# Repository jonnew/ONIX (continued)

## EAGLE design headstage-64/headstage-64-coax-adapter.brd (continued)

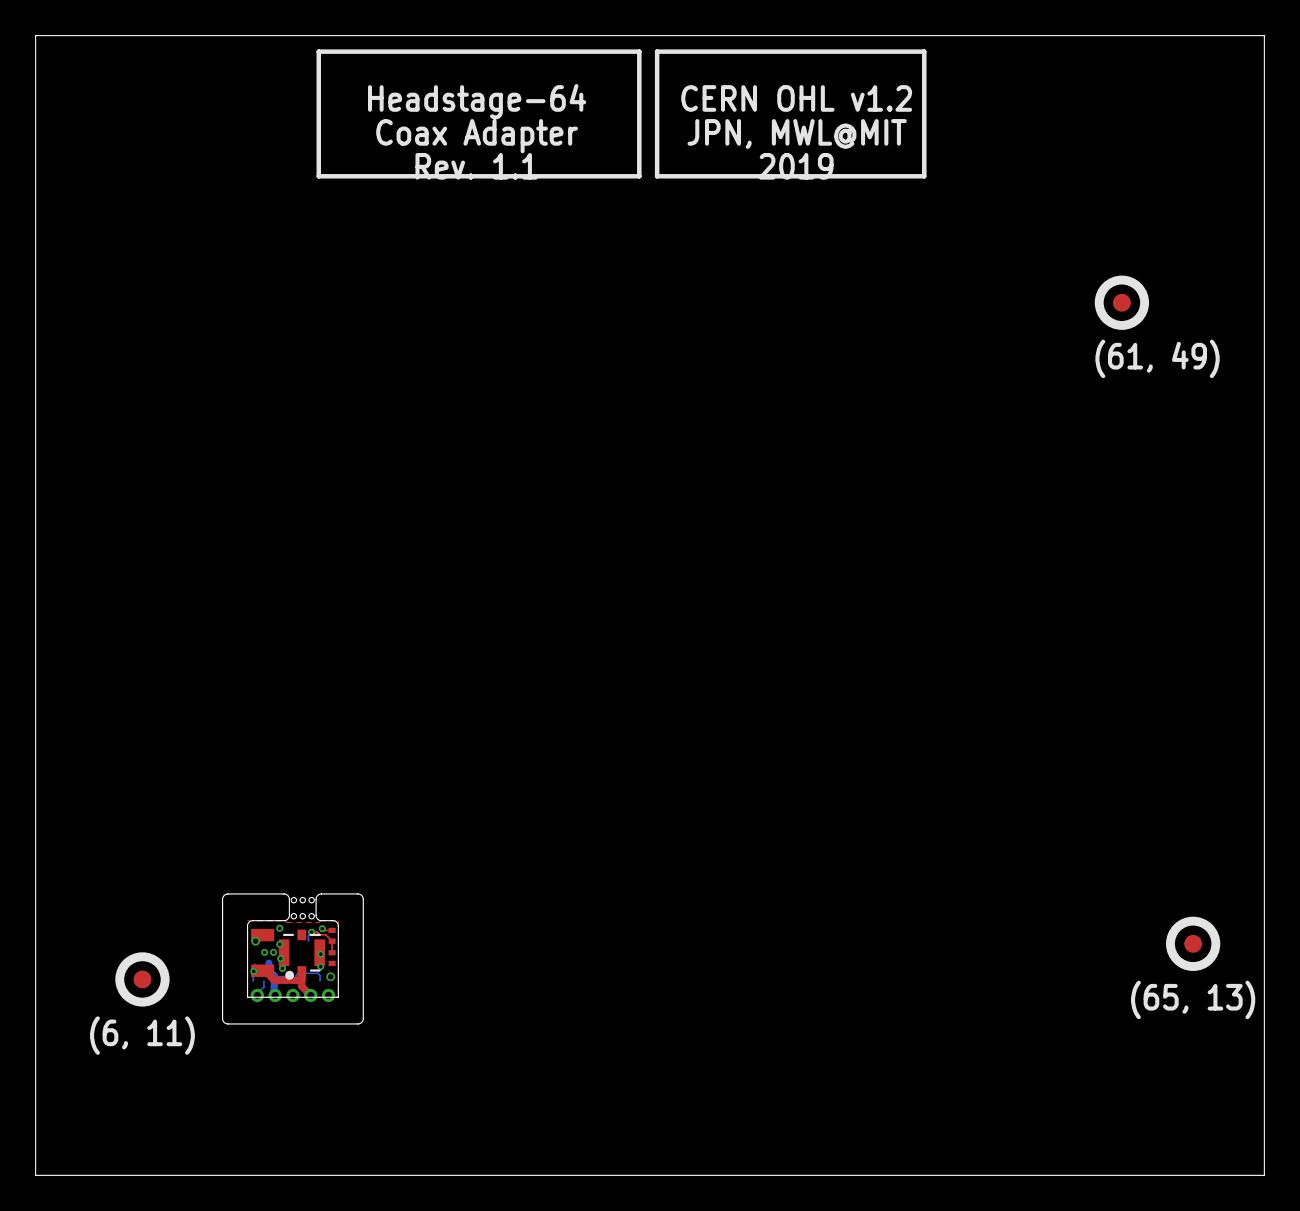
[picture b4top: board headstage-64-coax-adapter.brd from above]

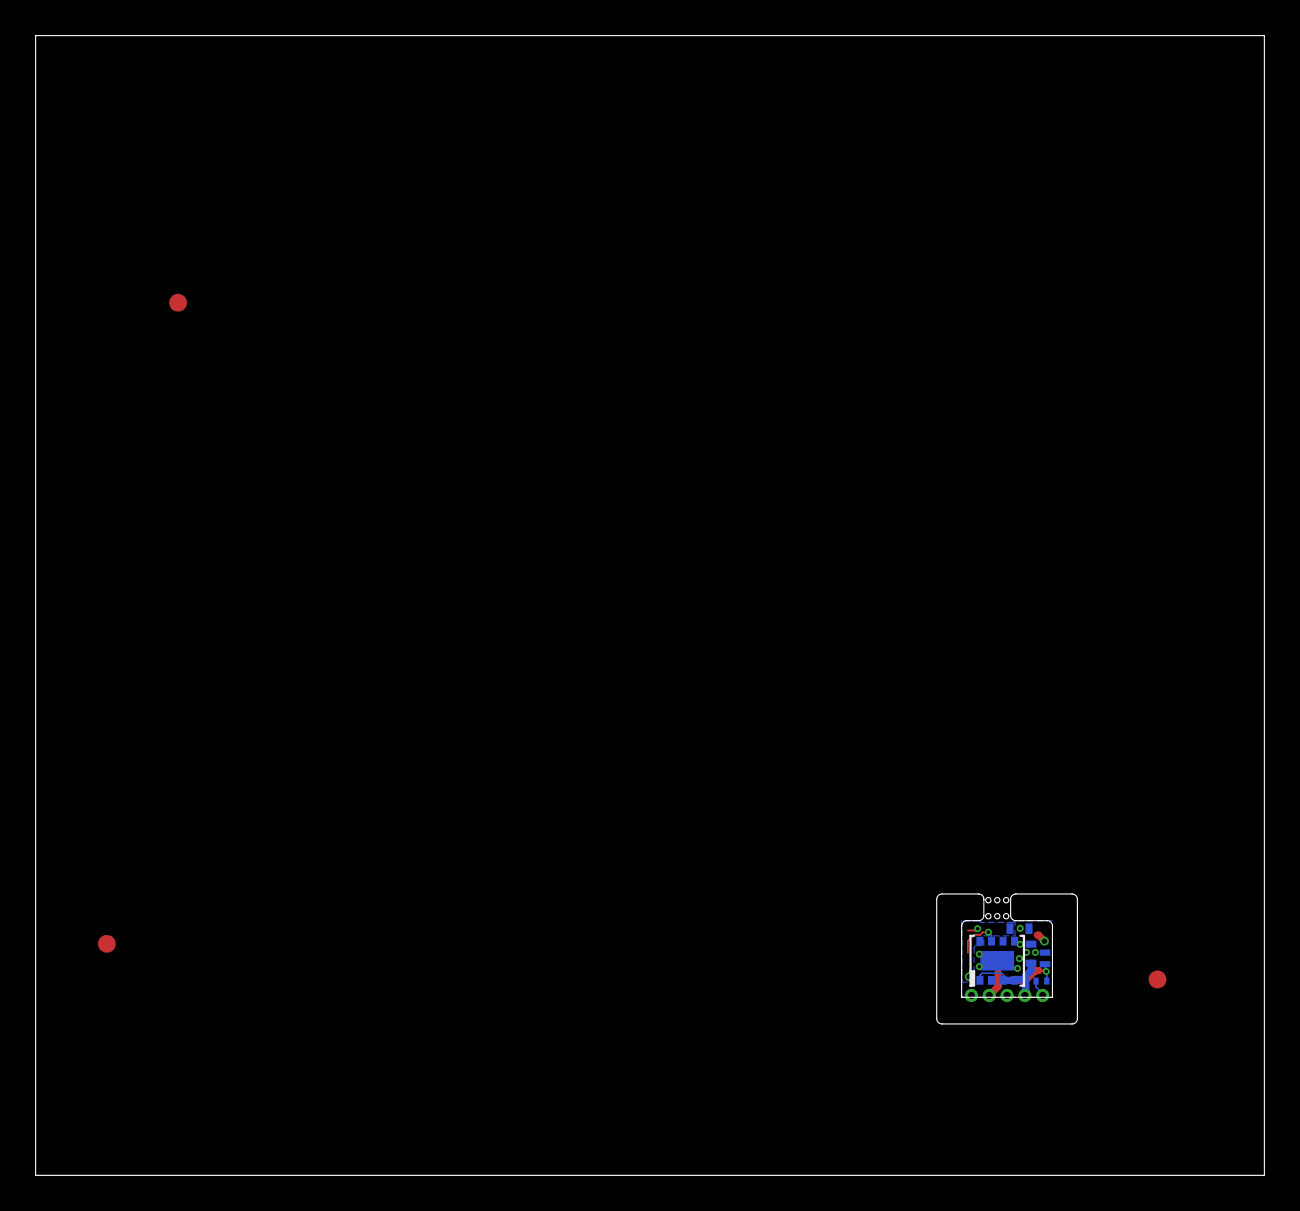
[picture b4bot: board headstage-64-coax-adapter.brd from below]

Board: 4 copper layers, 69.0 x 64.0 mm, 13 parts (5 on the bottom side), 6 nets.

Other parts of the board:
E$1, E$2, E$4: FIDUCIAL

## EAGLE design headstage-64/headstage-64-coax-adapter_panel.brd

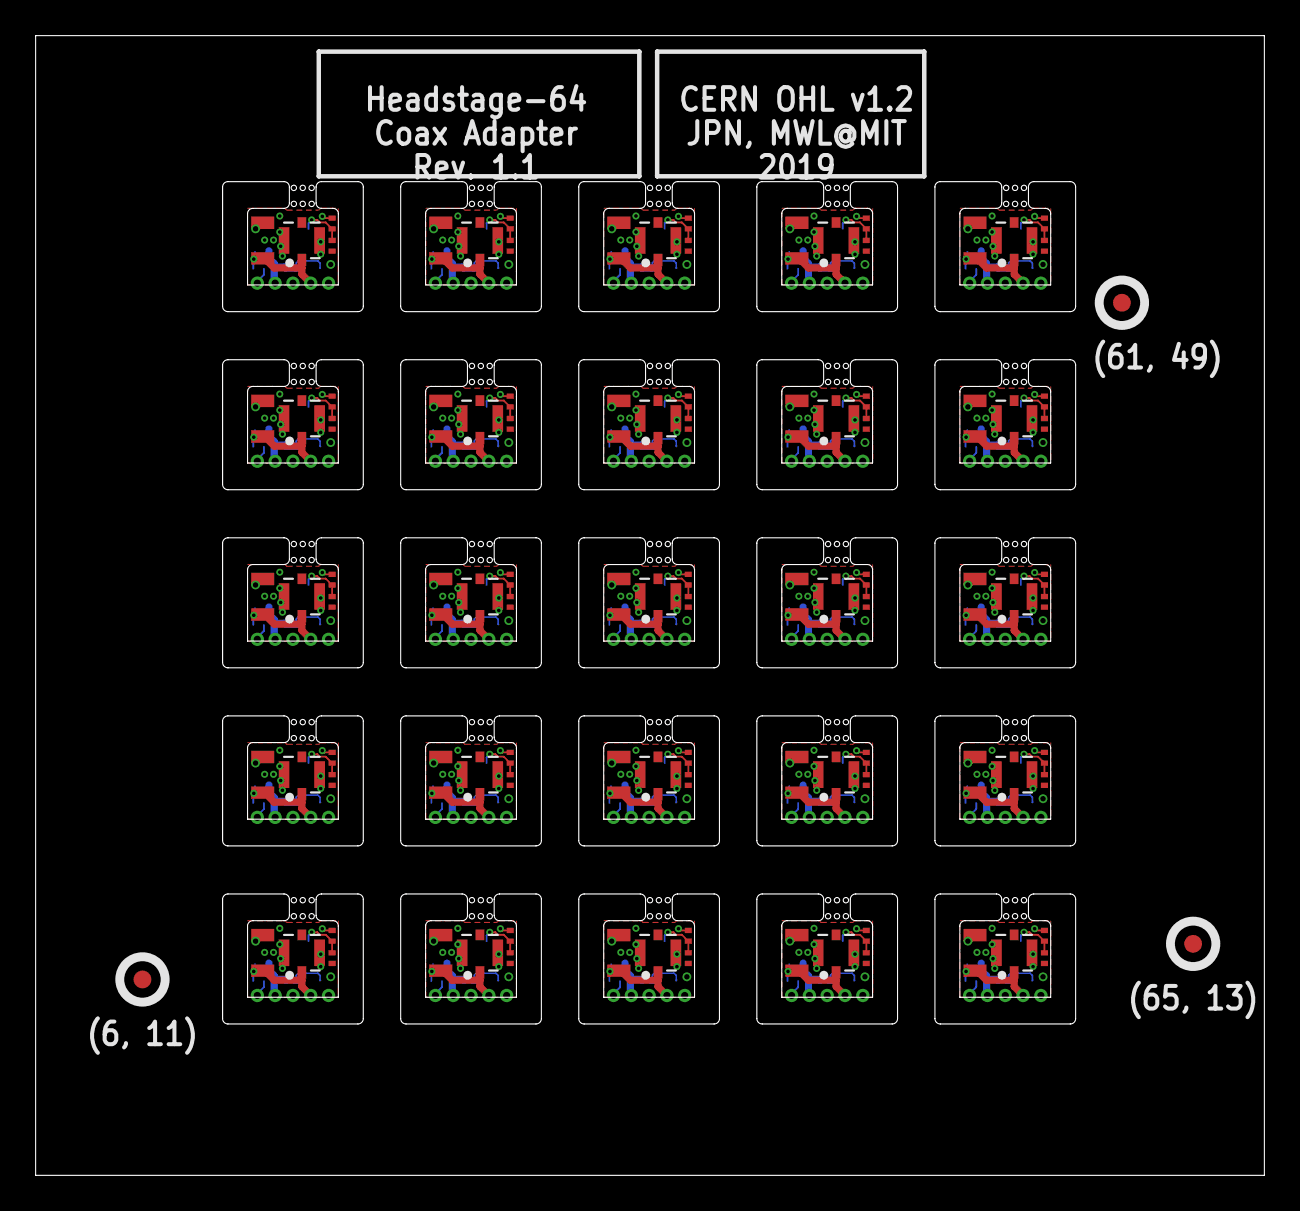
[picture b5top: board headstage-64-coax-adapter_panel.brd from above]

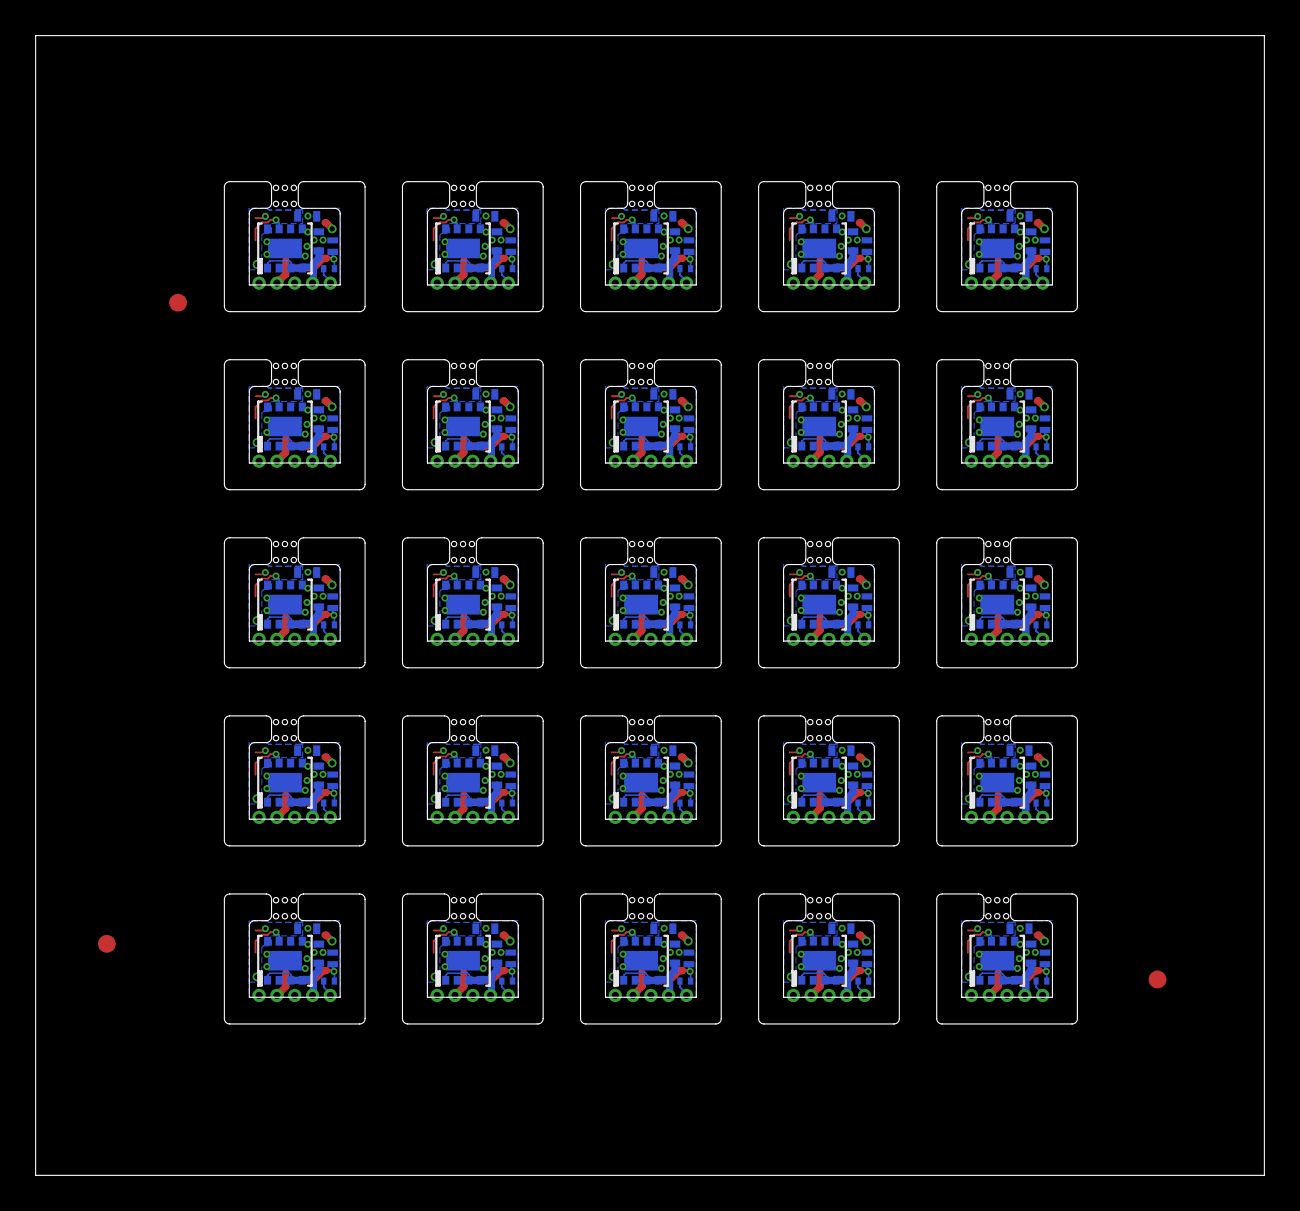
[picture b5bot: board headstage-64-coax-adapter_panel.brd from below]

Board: 4 copper layers, 69.0 x 64.0 mm, 253 parts (125 on the bottom side), 150 nets.

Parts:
C1, C2, C3, C4, C5, C6, C7, C8, C9, C10, C11, C12, C13, C14, C15, C16, C17, C18, C19, C20, C21, C22, C23, C24, C25, C26, C27, C28, C29, C30, C31, C32, C33, C34, C35, C36, C37, C38, C39, C40, C41, C42, C43, C44, C45, C46, C47, C48, C49, C50: 10uF; 0402T
D1, D2, D3, D4, D5, D6, D7, D8, D9, D10, D11, D12, D13, D14, D15, D16, D17, D18, D19, D20, D21, D22, D23, D24, D25: SESD0402X1UN-0020-090; 0402T-DFN
E$1, E$2, E$4: FIDUCIAL
J1, J3, J5, J7, J9, J11, J13, J15, J17, J19, J21, J23, J25, J27, J29, J31, J33, J35, J37, J39, J41, J43, J45, J47, J49: X.FL-R-SMT-1(02); X_FL_R_SMT_1(02)
J2, J4, J6, J8, J10, J12, J14, J16, J18, J20, J22, J24, J26, J28, J30, J32, J34, J36, J38, J40, J42, J44, J46, J48, J50: HEADSTAGE-64-REV1.4-DAUGHTER-CARD-CASTELLATED
L1, L2, L3, L4, L5, L6, L7, L8, L9, L10, L11, L12, L13, L14, L15, L16, L17, L18, L19, L20, L21, L22, L23, L24, L25: CIG21L4R7MNE; 0805T
R1, R4, R7, R10, R13, R16, R19, R22, R25, R28, R31, R34, R37, R40, R43, R46, R49, R52, R55, R58, R61, R64, R67, R70, R73: 1k; 0201T
R2, R5, R8, R11, R14, R17, R20, R23, R26, R29, R32, R35, R38, R41, R44, R47, R50, R53, R56, R59, R62, R65, R68, R71, R74: 143k; 0201T
R3, R6, R9, R12, R15, R18, R21, R24, R27, R30, R33, R36, R39, R42, R45, R48, R51, R54, R57, R60, R63, R66, R69, R72, R75: 24k; 0201T
U1, U2, U3, U4, U5, U6, U7, U8, U9, U10, U11, U12, U13, U14, U15, U16, U17, U18, U19, U20, U21, U22, U23, U24, U25: TPS82085; MICROSIP9-2.8X3

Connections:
GND: C1.2, C2.2, D1.A, J1.P$2, J1.P$3, J1.P$4, J2.5, R3.1, U1.5, U1.6, U1.PAD
GND2: C3.2, C4.2, D2.A, J3.P$2, J3.P$3, J3.P$4, J4.5, R6.1, U2.5, U2.6, U2.PAD
GND10: C5.2, C6.2, D3.A, J5.P$2, J5.P$3, J5.P$4, J6.5, R9.1, U3.5, U3.6, U3.PAD
GND12: C7.2, C8.2, D4.A, J7.P$2, J7.P$3, J7.P$4, J8.5, R12.1, U4.5, U4.6, U4.PAD
GND14: C9.2, C10.2, D5.A, J9.P$2, J9.P$3, J9.P$4, J10.5, R15.1, U5.5, U5.6, U5.PAD
GND16: C11.2, C12.2, D6.A, J11.P$2, J11.P$3, J11.P$4, J12.5, R18.1, U6.5, U6.6, U6.PAD
GND18: C13.2, C14.2, D7.A, J13.P$2, J13.P$3, J13.P$4, J14.5, R21.1, U7.5, U7.6, U7.PAD
GND20: C15.2, C16.2, D8.A, J15.P$2, J15.P$3, J15.P$4, J16.5, R24.1, U8.5, U8.6, U8.PAD
GND22: C17.2, C18.2, D9.A, J17.P$2, J17.P$3, J17.P$4, J18.5, R27.1, U9.5, U9.6, U9.PAD
GND24: C19.2, C20.2, D10.A, J19.P$2, J19.P$3, J19.P$4, J20.5, R30.1, U10.5, U10.6, U10.PAD
GND26: C21.2, C22.2, D11.A, J21.P$2, J21.P$3, J21.P$4, J22.5, R33.1, U11.5, U11.6, U11.PAD
GND28: C23.2, C24.2, D12.A, J23.P$2, J23.P$3, J23.P$4, J24.5, R36.1, U12.5, U12.6, U12.PAD
GND30: C25.2, C26.2, D13.A, J25.P$2, J25.P$3, J25.P$4, J26.5, R39.1, U13.5, U13.6, U13.PAD
GND32: C27.2, C28.2, D14.A, J27.P$2, J27.P$3, J27.P$4, J28.5, R42.1, U14.5, U14.6, U14.PAD
GND34: C29.2, C30.2, D15.A, J29.P$2, J29.P$3, J29.P$4, J30.5, R45.1, U15.5, U15.6, U15.PAD
GND36: C31.2, C32.2, D16.A, J31.P$2, J31.P$3, J31.P$4, J32.5, R48.1, U16.5, U16.6, U16.PAD
GND38: C33.2, C34.2, D17.A, J33.P$2, J33.P$3, J33.P$4, J34.5, R51.1, U17.5, U17.6, U17.PAD
GND40: C35.2, C36.2, D18.A, J35.P$2, J35.P$3, J35.P$4, J36.5, R54.1, U18.5, U18.6, U18.PAD
GND42: C37.2, C38.2, D19.A, J37.P$2, J37.P$3, J37.P$4, J38.5, R57.1, U19.5, U19.6, U19.PAD
GND44: C39.2, C40.2, D20.A, J39.P$2, J39.P$3, J39.P$4, J40.5, R60.1, U20.5, U20.6, U20.PAD
GND45: C41.2, C42.2, D21.A, J41.P$2, J41.P$3, J41.P$4, J42.5, R63.1, U21.5, U21.6, U21.PAD
GND46: C43.2, C44.2, D22.A, J43.P$2, J43.P$3, J43.P$4, J44.5, R66.1, U22.5, U22.6, U22.PAD
GND47: C45.2, C46.2, D23.A, J45.P$2, J45.P$3, J45.P$4, J46.5, R69.1, U23.5, U23.6, U23.PAD
GND48: C47.2, C48.2, D24.A, J47.P$2, J47.P$3, J47.P$4, J48.5, R72.1, U24.5, U24.6, U24.PAD
GND49: C49.2, C50.2, D25.A, J49.P$2, J49.P$3, J49.P$4, J50.5, R75.1, U25.5, U25.6, U25.PAD
unnamed: J4.1, L2.2, R4.2
unnamed: R2.1, R3.2, U1.7
unnamed: R5.1, R6.2, U2.7
unnamed: J6.1, L3.2, R7.2
unnamed: R8.1, R9.2, U3.7
unnamed: J8.1, L4.2, R10.2
unnamed: R11.1, R12.2, U4.7
unnamed: J10.1, L5.2, R13.2
unnamed: R14.1, R15.2, U5.7
unnamed: J12.1, L6.2, R16.2
unnamed: R17.1, R18.2, U6.7
unnamed: J14.1, L7.2, R19.2
unnamed: R20.1, R21.2, U7.7
unnamed: J16.1, L8.2, R22.2
unnamed: R23.1, R24.2, U8.7
unnamed: J18.1, L9.2, R25.2
unnamed: R26.1, R27.2, U9.7
unnamed: J20.1, L10.2, R28.2
unnamed: R29.1, R30.2, U10.7
unnamed: J22.1, L11.2, R31.2
unnamed: R32.1, R33.2, U11.7
unnamed: J24.1, L12.2, R34.2
unnamed: R35.1, R36.2, U12.7
unnamed: J26.1, L13.2, R37.2
unnamed: R38.1, R39.2, U13.7
unnamed: J28.1, L14.2, R40.2
unnamed: R41.1, R42.2, U14.7
unnamed: J30.1, L15.2, R43.2
unnamed: R44.1, R45.2, U15.7
unnamed: J32.1, L16.2, R46.2
unnamed: R47.1, R48.2, U16.7
unnamed: J34.1, L17.2, R49.2
unnamed: R50.1, R51.2, U17.7
unnamed: J36.1, L18.2, R52.2
unnamed: R53.1, R54.2, U18.7
unnamed: J38.1, L19.2, R55.2
unnamed: R56.1, R57.2, U19.7
unnamed: J40.1, L20.2, R58.2
unnamed: R59.1, R60.2, U20.7
unnamed: J42.1, L21.2, R61.2
unnamed: R62.1, R63.2, U21.7
unnamed: J44.1, L22.2, R64.2
unnamed: R65.1, R66.2, U22.7
unnamed: J46.1, L23.2, R67.2
unnamed: R68.1, R69.2, U23.7
unnamed: J48.1, L24.2, R70.2
unnamed: R71.1, R72.2, U24.7
unnamed: J2.1, L1.2, R1.2
unnamed: J50.1, L25.2, R73.2
unnamed: R74.1, R75.2, U25.7
SIGOUT: D1.C, J1.P$1, J2.4, L1.1, R1.1
SIGOUT1: D2.C, J3.P$1, J4.4, L2.1, R4.1
SIGOUT2: D3.C, J5.P$1, J6.4, L3.1, R7.1
SIGOUT3: D4.C, J7.P$1, J8.4, L4.1, R10.1
SIGOUT4: D5.C, J9.P$1, J10.4, L5.1, R13.1
SIGOUT5: D6.C, J11.P$1, J12.4, L6.1, R16.1
SIGOUT6: D7.C, J13.P$1, J14.4, L7.1, R19.1
SIGOUT7: D8.C, J15.P$1, J16.4, L8.1, R22.1
SIGOUT8: D9.C, J17.P$1, J18.4, L9.1, R25.1
SIGOUT9: D10.C, J19.P$1, J20.4, L10.1, R28.1
SIGOUT10: D11.C, J21.P$1, J22.4, L11.1, R31.1
SIGOUT11: D12.C, J23.P$1, J24.4, L12.1, R34.1
SIGOUT12: D13.C, J25.P$1, J26.4, L13.1, R37.1
SIGOUT13: D14.C, J27.P$1, J28.4, L14.1, R40.1
SIGOUT14: D15.C, J29.P$1, J30.4, L15.1, R43.1
SIGOUT15: D16.C, J31.P$1, J32.4, L16.1, R46.1
SIGOUT16: D17.C, J33.P$1, J34.4, L17.1, R49.1
SIGOUT17: D18.C, J35.P$1, J36.4, L18.1, R52.1
SIGOUT18: D19.C, J37.P$1, J38.4, L19.1, R55.1
SIGOUT19: D20.C, J39.P$1, J40.4, L20.1, R58.1
SIGOUT20: D21.C, J41.P$1, J42.4, L21.1, R61.1
SIGOUT21: D22.C, J43.P$1, J44.4, L22.1, R64.1
SIGOUT22: D23.C, J45.P$1, J46.4, L23.1, R67.1
SIGOUT23: D24.C, J47.P$1, J48.4, L24.1, R70.1
SIGOUT24: D25.C, J49.P$1, J50.4, L25.1, R73.1
VCOAX: C2.1, J2.3, R2.2, U1.8
VCOAX1: C3.1, J4.3, R5.2, U2.8
VCOAX2: C5.1, J6.3, R8.2, U3.8
VCOAX3: C7.1, J8.3, R11.2, U4.8
VCOAX4: C9.1, J10.3, R14.2, U5.8
VCOAX5: C11.1, J12.3, R17.2, U6.8
VCOAX6: C13.1, J14.3, R20.2, U7.8
VCOAX7: C15.1, J16.3, R23.2, U8.8
VCOAX8: C17.1, J18.3, R26.2, U9.8
VCOAX9: C19.1, J20.3, R29.2, U10.8
VCOAX10: C21.1, J22.3, R32.2, U11.8
VCOAX11: C23.1, J24.3, R35.2, U12.8
VCOAX12: C25.1, J26.3, R38.2, U13.8
VCOAX13: C27.1, J28.3, R41.2, U14.8
VCOAX14: C29.1, J30.3, R44.2, U15.8
VCOAX15: C31.1, J32.3, R47.2, U16.8
VCOAX16: C33.1, J34.3, R50.2, U17.8
VCOAX17: C35.1, J36.3, R53.2, U18.8
VCOAX18: C37.1, J38.3, R56.2, U19.8
VCOAX19: C39.1, J40.3, R59.2, U20.8
VCOAX20: C41.1, J42.3, R62.2, U21.8
VCOAX21: C43.1, J44.3, R65.2, U22.8
VCOAX22: C45.1, J46.3, R68.2, U23.8
VCOAX23: C47.1, J48.3, R71.2, U24.8
VCOAX24: C49.1, J50.3, R74.2, U25.8
VRAW: C1.1, J2.2, U1.1, U1.3, U1.4
VRAW1: C4.1, J4.2, U2.1, U2.3, U2.4
VRAW2: C6.1, J6.2, U3.1, U3.3, U3.4
VRAW3: C8.1, J8.2, U4.1, U4.3, U4.4
VRAW4: C10.1, J10.2, U5.1, U5.3, U5.4
VRAW5: C12.1, J12.2, U6.1, U6.3, U6.4
VRAW6: C14.1, J14.2, U7.1, U7.3, U7.4
VRAW7: C16.1, J16.2, U8.1, U8.3, U8.4
VRAW8: C18.1, J18.2, U9.1, U9.3, U9.4
VRAW9: C20.1, J20.2, U10.1, U10.3, U10.4
VRAW10: C22.1, J22.2, U11.1, U11.3, U11.4
VRAW11: C24.1, J24.2, U12.1, U12.3, U12.4
VRAW12: C26.1, J26.2, U13.1, U13.3, U13.4
VRAW13: C28.1, J28.2, U14.1, U14.3, U14.4
VRAW14: C30.1, J30.2, U15.1, U15.3, U15.4
VRAW15: C32.1, J32.2, U16.1, U16.3, U16.4
VRAW16: C34.1, J34.2, U17.1, U17.3, U17.4
VRAW17: C36.1, J36.2, U18.1, U18.3, U18.4
VRAW18: C38.1, J38.2, U19.1, U19.3, U19.4
VRAW19: C40.1, J40.2, U20.1, U20.3, U20.4
VRAW20: C42.1, J42.2, U21.1, U21.3, U21.4
VRAW21: C44.1, J44.2, U22.1, U22.3, U22.4
VRAW22: C46.1, J46.2, U23.1, U23.3, U23.4
VRAW23: C48.1, J48.2, U24.1, U24.3, U24.4
VRAW24: C50.1, J50.2, U25.1, U25.3, U25.4

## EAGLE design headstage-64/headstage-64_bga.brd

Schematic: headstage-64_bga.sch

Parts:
C1, C3, C5, C46, C55, C68, C74: 1uF; 0201T; PARTNO CL03A105MP3ZSNH
C2, C4, C6, C12, C13, C70: 0.1uF; 0201T; PARTNO C0603X5R1C104K030BC
C7, C8, C11, C20, C21: 0.1uF; 0201T; PARTNO CL03A104KA3NNNC
C9: 470pF; 0201T
C10: 0.1uF; 0201T; PARTNP CL03A104KA3NNNC
C14, C15, C16, C23, C54, C69, C75, C76: 1uF; 0402T; PARTNO CL05A105KO5NNNC
C17, C18: 0.22uF; 0402T; PARTNO UMK105BJ224KV-F
C19: 10pF; 0201T
C22, C24, C42, C77: 10uF; 0402T; PARTNO CL05A106MQ5NUNC
C25: 4.7uF; 0402T; PARTNO CL05A475MO5NUNC
C26: 0.1uF; 0402T; PARTNO C0603X5R1C104K030BC
C27, C38, C43, C47, C49, C50, C57, C62, C65: 10nF; 0201T
C28, C34: 47nF; 0201T
C29, C31, C32, C37: 4.7nF; 0201T
C30: 10nF; 0201T; PARTNO GRM033R71E103KE14D
C33, C39, C44, C71: 22nF; 0201T
C35: 2.2nF; 0201T
C36, C48, C56, C58, C60, C61, C64, C67, C73: 0.1uF; 0201T
C40, C45, C72: 0.47uF; 0201T; PARTNO GRM033R60J474KE90D
C41: 22uF; 0402T; PARTNO CL05A226MQ6ZUN8
C51: 0.1uF; 0201T; PARTNO C1005X7R1H104K050BB
C52: 47nF; 0201T; PARTNO C1005X7R1H473K050BB
C53: 22uF; 0402T; PARTNO CL05A226MQ5QUNC
C59, C63: 4.7uF; 0402T; PARTNO GRM155R61A475MEAAD
C66: 10nF; 0201T; PARTNO CL03B103KP3NNNC
D1, D2, D3: PHOTODIODE_0805T; 0805T
D4: VSKY05401006; 0402T
D5, D6: XZVGR155W; LED-0201T
J1: HEADSTAGE64_EDGE-MOUNT; HEADSTAGE64-EDGE-MOUNT_PADS
J2: HEADSTAGE64_EDGE-MOUNT_CASTELLATED; HEADSTAGE64-EDGE-MOUNT_CASTELLATED
J3: GND_LINK_0201; 0201_LINK
L1, L2: MLZ2012M100WT000; 0805T
L3: CIG21L4R7MNE; 0805T
L4: CBC3225T101MR; 1210T
L5, L6, L7: BLM15PX601SN1D; 0402T; PARTNO BLM15PX601SN1D
L12: BLM18KG601SN1D; 0603T
R1, R2, R3, R37: 15k; 0201T
R4, R5, R17, R18, R19, R23, R30, R31, R32, R34, R35, R36, R38: 10k; 0201T
R6: 5.49k; 0201T
R7: 220; 0201T
R8: 600; 0201T
R9, R11: 1M; 0201T
R10: 83.3k; 0201T
R12: 90.9k; 0201T
R13: 50; 0201T
R14, R15, R33: 1k; 0201T
R16: 49.9; 0201T
R20: 100k; 0201T
R21, R22: 4.7k; 0201T
R24, R25: 2k; 0201T
R26, R27, R28, R29: 100; 0201T
R39: 0 (DNP); 0201T
R40: 0; 0201T
TP1: VCC; B0.4MM
TP2: gnd; B0.4MM
TP3, TP4, TP5, TP6, TP12: TPB0.4MM; B0.4MM
TP7, TP9, TP11: TPTP06R; TP06R
TP8, TP10: VCC; B0.3MM
U1, U5, U6, U14: TS4231; WLCSP3X3
U2: MPU9250_QFN_NO-PAD; QFN24-3X3_NO-PAD
U3: CAT4016_QFN; QFN24-4X4; PARTNO CAT4016HV6-GT2
U4: OPA170; PDSO-N5; PARTNO OPA170AIDBVR
U7: RHD2164_BGA_BGA; BGA104_0.5MM
U8: ADG1401; LFCSP8-2X3; PARTNO ADG1401BCPZ
U9: TLV70725; X2SON
U10: TLV70718; X2SON
U11: 10M08DC; VBGA81-4X4
U12: LT3463; DFN103X3
U13: DAC5311; SC70
U15: INA826; PWSON-N8-3X3; PARTNO INA826AIDRGR
U16, U18: TLV70733; X2SON
U17: TLV70712; X2SON
U19: DS90UB913A_WQFN; WQFN32-5X5
U25: TPL0501_UQFN; UQFN; PARTNO TPL0501-100RSER
U$1: PINHD-2X35+4_DF40-70HEAD; DF40-70HEAD
X1: X.FL-R-SMT-1; X_FL_R_SMT_1(02)

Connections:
$N324: C37.1, C38.1, C39.1, C40.1, C42.1, L5.2, U11.A8 (VCCD_PLL2)
+1V2: C27.1, C29.1, C33.1, C34.1, C35.1, C36.1, C41.1, C68.1, L5.1, U11.B2 (VCC), U11.B9 (VCC), U11.H2 (VCC), U11.H8 (VCC), U17.1 (OUT)
+1V8: C55.1, C56.1, C57.1, L6.1, L7.1, R19.1, U10.1 (OUT), U19.28 (VDDD)
+2V5: C22.1, C32.1, C47.1, C71.1, C72.1, U9.1 (OUT), U11.B1 (VCCA3), U11.B8 (VCCA2), U11.J1 (VCCA1), U11.J9 (VCCA4)
+3V3: C2.1, C4.1, C6.1, C12.1, C13.1, C24.1, C28.1, C31.1, C43.1, C44.1, C45.1, C48.1, C50.1, C66.1, C67.1, C70.1, C74.1, J1.8, J2.8, R5.1, R18.1, R21.1, R22.1, R24.1, R25.1, R30.1, R31.1, R32.1, R35.1, R36.1, R38.1, R39.2, TP2.TP, U1.C3 (DVDD), U2.8 (VDDIO), U2.13 (VDD), U5.C3 (DVDD), U6.C3 (DVDD), U7.M16 (LVDS_EN), U11.D5 (VCCIO8), U11.E4 (VCCIO1_2), U11.E6 (VCCIO5_6), U11.F5 (VCCIO3), U13.4 (AVDD), U14.C3 (DVDD), U18.1 (OUT), U19.25 (VDDIO), U25.P$7 (VDD)
+3V3_AN: C77.1, R40.1, U16.1 (OUT)
AGND: C30.2, C73.1, C76.2, C77.2, J3.1, U7.M2 (VESD), U7.M17 (GND), U7.N1 (GND), U7.N6 (GND), U16.2 (GND), U16.5 (GND), U$1.70, U$1.M1, U$1.M2, U$1.M4
AUXIN2: TP10.TP, U7.N4 (AUXIN2)
AUXIN3: TP8.TP, U7.N5 (AUXIN3)
CONFIG_SEL: R34.1, U11.C6 (CONFIG_SEL/C6)
CONF_DONE: R36.2, U11.A2 (DIFFIO_RX_T24N/CONF_DONE/A2)
DAC_CS: U11.C4 (DIFFIO_RX_T26P/C4), U13.1 (!SYNC)
DATA1: U1.C1 (D/CFGDATA), U11.A4 (DIFFIO_RX_T19P/A4)
DATA2: U5.C1 (D/CFGDATA), U11.C3 (DIFFIO_RX_T26N/C3)
DATA3: U6.C1 (D/CFGDATA), U11.A7 (DIFFIO_RX_T16P/A7)
DATA4: U11.G3 (DIFFIO_RX_L27P/G3), U14.C1 (D/CFGDATA)
DIN0: U11.H6 (DIFFIO_TX_RX_B12N/H6), U19.19 (DIN0)
DIN1: U11.J6 (DIFFIO_TX_RX_B12P/J6), U19.20 (DIN1)
DIN2: U11.G6 (DIFFIO_TX_RX_B14N/G6), U19.21 (DIN2)
DIN3: U11.H7 (DIFFIO_TX_RX_B14P/H7), U19.22 (DIN3)
DIN4: U11.J7 (DIFFIO_TX_RX_B16N/J7), U19.23 (DIN4)
DIN5: U11.J8 (DIFFIO_TX_RX_B16P/J8), U19.24 (DIN5)
DIN6: U11.G7 (DIFFIO_RX_R1P/G7), U19.26 (DIN6)
DIN7: U11.F7 (DIFFIO_RX_R1N/F7), U19.27 (DIN7)
DIN8: U11.G8 (DIFFIO_RX_R7P/G8), U19.29 (DIN8)
DIN9: U11.G9 (DIFFIO_RX_R7N/G9), U19.30 (DIN9)
DIN10: U11.F8 (DIFFIO_RX_R10P/F8), U19.31 (DIN10)
DIN11: U11.F9 (DIFFIO_RX_R10N/F9), U19.32 (DIN11)
E0: U7.K2 (IN0), U$1.2
E1: U7.J1 (IN1), U$1.68
E2: U7.J2 (IN2), U$1.3
E3: U7.H1 (IN3), U$1.67
E4: U7.H2 (IN4), U$1.4
E5: U7.G1 (IN5), U$1.66
E6: U7.G2 (IN6), U$1.5
E7: U7.F1 (IN7), U$1.65
E8: U7.F2 (IN8), U$1.6
E9: U7.E1 (IN9), U$1.64
E10: U7.E2 (IN10), U$1.7
E11: U7.D1 (IN11), U$1.63
E12: U7.D2 (IN12), U$1.8
E13: U7.C1 (IN13), U$1.62
E14: U7.C2 (IN14), U$1.9
E15: U7.B1 (IN15), U$1.61
E16: U7.A1 (IN16), U$1.10
E17: U7.B2 (IN17), U$1.60
E18: U7.A2 (IN18), U$1.11
E19: U7.B3 (IN19), U$1.59
E20: U7.A3 (IN20), U$1.12
E21: U7.B4 (IN21), U$1.58
E22: U7.A4 (IN22), U$1.13
E23: U7.B5 (IN23), U$1.57
E24: U7.A5 (IN24), U$1.14
E25: U7.B6 (IN25), U$1.56
E26: U7.A6 (IN26), U$1.15
E27: U7.B7 (IN27), U$1.55
E28: U7.A7 (IN28), U$1.16
E29: U7.B8 (IN29), U$1.54
E30: U7.A8 (IN30), U$1.17
E31: U7.B9 (IN31), U$1.53
E32: U7.A9 (IN32), U$1.18
E33: U7.A10 (IN33), U$1.52
E34: U7.B10 (IN34), U$1.19
E35: U7.A11 (IN35), U$1.51
E36: U7.B11 (IN36), U$1.20
E37: U7.A12 (IN37), U$1.50
E38: U7.B12 (IN38), U$1.21
E39: U7.A13 (IN39), U$1.49
E40: U7.B13 (IN40), U$1.22
E41: U7.A14 (IN41), U$1.48
E42: U7.B14 (IN42), U$1.23
E43: U7.A15 (IN43), U$1.47
E44: U7.B15 (IN44), U$1.24
E45: U7.A16 (IN45), U$1.46
E46: U7.B16 (IN46), U$1.25
E47: U7.A17 (IN47), U$1.45
E48: U7.B17 (IN48), U$1.26
E49: U7.C16 (IN49), U$1.44
E50: U7.C17 (IN50), U$1.27
E51: U7.D16 (IN51), U$1.43
E52: U7.D17 (IN52), U$1.28
E53: U7.E16 (IN53), U$1.42
E54: U7.E17 (IN54), U$1.29
E55: U7.F16 (IN55), U$1.41
E56: U7.F17 (IN56), U$1.30
E57: U7.G16 (IN57), U$1.40
E58: U7.G17 (IN58), U$1.31
E59: U7.H16 (IN59), U$1.39
E60: U7.H17 (IN60), U$1.32
E61: U7.J16 (IN61), U$1.38
E62: U7.J17 (IN62), U$1.33
E63: U7.K16 (IN63), U$1.37
ENV1: U1.C2 (E/CFGCLK), U11.H3 (DIFFIO_TX_RX_B1N/H3)
ENV2: U5.C2 (E/CFGCLK), U11.G4 (DIFFIO_TX_RX_B3N/G4)
ENV3: U6.C2 (E/CFGCLK), U11.G5 (DIFFIO_TX_RX_B3P/G5)
ENV4: U14.C2 (E/CFGCLK)
ESTIM_POW_EN: R17.1, U12.8 (!SHDN2), U12.9 (!SHDN1)
GND: C1.2, C2.2, C3.2, C4.2, C5.2, C6.2, C7.2, C8.2, C10.2, C11.2, C12.2, C13.2, C15.2, C16.2, C17.2, C18.2, C20.2, C21.2, C22.2, C23.2, C24.2, C25.2, C26.2, C27.2, C28.2, C29.2, C31.2, C32.2, C33.2, C34.2, C35.2, C36.2, C37.2, C38.2, C39.2, C40.2, C41.2, C42.2, C43.2, C44.2, C45.2, C46.2, C47.2, C48.2, C49.2, C50.2, C53.2, C54.2, C55.2, C56.2, C57.2, C58.2, C59.2, C60.2, C61.2, C62.2, C63.2, C64.2, C65.2, C66.2, C67.2, C68.2, C69.2, C70.2, C71.2, C72.2, C74.2, C75.2, J1.4, J1.5, J2.4, J2.5, J3.2, R1.1, R2.1, R3.1, R12.1, R13.1, R16.1, R17.2, R20.2, R23.2, R33.2, R34.2, R37.1, TP1.TP, U1.B2 (AVSS), U1.B3 (AVSS2), U2.11 (FSYNC), U2.18 (GND), U3.1 (GND), U3.PAD (GND), U5.B2 (AVSS), U5.B3 (AVSS2), U6.B2 (AVSS), U6.B3 (AVSS2), U8.3 (GND), U9.2 (GND), U9.5 (GND), U10.2 (GND), U10.5 (GND), U11.A1 (GND), U11.A9 (GND), U11.B4 (GND), U11.D1 (GND), U11.D7 (GND), U11.E5 (GND), U11.E9 (GND), U11.F4 (GND), U11.F6 (GND), U11.H1 (GND), U11.H5 (GND), U11.H9 (GND), U12.PAD (GND), U13.5 (GND), U14.B2 (AVSS), U14.B3 (AVSS2), U15.6 (REF), U17.2 (GND), U17.5 (GND), U18.2 (GND), U18.5 (GND), U19.6 (ID), U19.7 (RES), U19.PAD (GND), U25.P$4 (GND), U25.P$8 (LA), X1.P$2 (2), X1.P$3 (2), X1.P$4 (2)
GPO0: TP7.TP, U19.15 (GPIO0)
HSYNC: U11.J5 (DIFFIO_TX_RX_B9P/J5), U19.1 (HSYNC)
IMU_CS: U2.22 (!CS), U11.A3
INTAN_VDD: C73.2, R39.1, R40.2, U7.M15 (VDD), U7.N2 (VDD), U7.N15 (VDD)
ISTIM: R7.1, U8.1 (S), U15.1 (-IN), U$1.1
JTAGEN: R30.2, U11.D2 (JTAGEN/D2)
LED-1: U3.5 (LED1), U3.6 (LED2), U3.7 (LED3), U3.8 (LED4), U3.9 (LED5), U3.10 (LED6), U3.11 (LED7), U3.12 (LED8), U$1.34
LED-2: U3.13 (LED9), U3.14 (LED10), U3.15 (LED11), U3.16 (LED12), U3.17 (LED13), U3.18 (LED14), U3.19 (LED15), U3.20 (LED16), U$1.35
LED_CLK: U3.3 (CLK), U11.F2 (DIFFIO_RX_L18P/CLK0P/F2)
LED_LATCH: U3.4 (LATCH), U11.G2 (DIFFIO_RX_L20N/CLK1N/G2)
LED_SIN: U3.2 (SIN), U11.F1 (DIFFIO_RX_L18N/CLK0N/F1)
MIDFILT: J1.1, J2.1, L3.2, L4.1, R14.1, R15.2
unnamed: R8.2, U25.P$6 (WA)
unnamed: C14.1, L2.1, U12.4 (SW2)
unnamed: C19.1, R10.1, R11.2, U12.6 (FB2)
unnamed: D1.2 (C), U1.A3 (IIN-)
unnamed: D1.1 (A), U1.A2 (IIN+)
unnamed: R1.2, U1.B1 (RBIAS)
unnamed: C3.1, U1.A1 (AVDD)
unnamed: L1.1, U12.2 (SW1)
unnamed: D2.2 (C), U5.A3 (IIN-)
unnamed: D2.1 (A), U5.A2 (IIN+)
unnamed: R2.2, U5.B1 (RBIAS)
unnamed: C1.1, U5.A1 (AVDD)
unnamed: C25.1, C26.1, L4.2, L12.1, R14.2
unnamed: R8.1, U3.23 (RSET)
unnamed: D3.2 (C), U6.A3 (IIN-)
unnamed: D3.1 (A), U6.A2 (IIN+)
unnamed: R3.2, U6.B1 (RBIAS)
unnamed: C5.1, U6.A1 (AVDD)
unnamed: C14.2, D4.2 (C), U12.5 (D2)
unnamed: R6.2, U15.2 (RG1)
unnamed: R6.1, U15.3 (RG2)
unnamed: C9.2, R7.2, U4.4 (OUT), U15.4 (+IN)
unnamed: R13.2, U8.8 (D)
unnamed: R9.1, R12.2, U12.10 (FB1)
unnamed: C9.1, R4.1, R5.2, U4.3 (-IN)
unnamed: TP9.TP, U14.A3 (IIN-)
unnamed: R10.2, U12.7 (VREF)
unnamed: C51.2, U19.13 (DOUT+)
unnamed: D5.2 (A), R24.2
unnamed: R18.2, U19.9 (PDB)
unnamed: C52.2, U19.12 (DOUT-)
unnamed: C52.1, R16.2
unnamed: R19.2, R20.1, U19.8 (MODE)
unnamed: C59.1, C61.1, C62.1, L6.2, U19.10 (VDDPLL)
unnamed: C49.1, C53.1, C58.1, L7.2, U19.14 (VDDCML)
unnamed: C30.1, U7.N17 (ADC_REF)
unnamed: C63.1, C64.1, C65.1, U19.11 (VDDT)
unnamed: TP11.TP, U14.A2 (IIN+)
unnamed: D6.2 (A), R25.2
unnamed: C60.1, U2.10 (REGOUT)
unnamed: R37.2, U14.B1 (RBIAS)
unnamed: C46.1, U14.A1 (AVDD)
unnamed: R38.2, U11.D6 (NCONFIG/D6)
NSTATUS: R35.2, U11.B3 (DIFFIO_RX_T24P/NSTATUS/B3)
PCLK: U11.H4 (DIFFIO_TX_RX_B5P/H4), U19.3 (PCLK1)
POT_CS: U11.G1 (DIFFIO_RX_L20P/CLK1P/G1), U25.P$3 (!CS)
REF: U7.M1 (REF_ELEC), U$1.69
RHD_CLK_N: R28.1, U7.N9 (SCLK-), U11.D9 (DIFFIO_RX_R16N/CLK3N/D9)
RHD_CLK_P: R28.2, U7.N10 (SCLK+), U11.D8 (DIFFIO_RX_R16P/CLK3P/D8)
RHD_CS_N: R26.1, U7.N7 (!CS!-), U11.E7 (DIFFIO_RX_R14N/CLK2N/E7)
RHD_CS_P: R26.2, U7.N8 (!CS!+), U11.E8 (DIFFIO_RX_R14P/CLK2P/E8)
RHD_MISO_N: R27.1, U7.N13 (MISO-), U11.B7 (DIFFIO_RX_R33N/PLL_R_CLKOUTN/B7)
RHD_MISO_P: R27.2, U7.N14 (MISO+), U11.C7 (DIFFIO_RX_R33P/PLL_R_CLKOUTP/C7)
RHD_MOSI_N: R29.1, U7.N11 (MOSI-), U11.C9 (DIFFIO_RX_R27N/C9)
RHD_MOSI_P: R29.2, U7.N12 (MOSI+), U11.C8 (DIFFIO_RX_R27P/C8)
SCL: R22.2, U11.J3 (DIFFIO_TX_RX_B5N/J3), U19.4 (SCL)
SCLK: U2.23 (SCL/SCLK), U11.F3 (DIFFIO_RX_L27N/F3), U13.2 (SCLK), U25.P$5 (SCLK)
SDA: R21.2, U11.J2 (DIFFIO_TX_RX_B1P/J2), U19.5 (SDA)
SDI: U2.24 (SDA/SDI), U11.B5 (DIFFIO_RX_T19N/B5), U25.P$2 (DIN)
SDO: U2.9 (AD0/SDO), U11.E3, U13.3 (DIN)
SIGOUT: C51.1, J1.3, J2.3, L3.1, R15.1, X1.P$1 (1)
STATUS_A: D6.1 (C), J1.6, J2.6, U11.C2 (DIFFIO_RX_L1N/C2)
STATUS_B: D5.1 (C), J1.7, J2.7, U11.C1 (DIFFIO_RX_L1P/C1)
STIM_NULL: R23.1, U8.6 (IN), U11.A5 (DIFFIO_RX_T18N/A5)
TCK: R33.1, TP5.TP, U11.D4 (DIFFIO_RX_L11P/TCK/D4)
TDI: R32.2, TP4.TP, U11.E1 (DIFFIO_RX_L12N/TDI/E1)
TDO: TP3.TP, U11.E2 (DIFFIO_RX_L12P/TDO/E2)
TMS: R31.2, TP6.TP, U11.D3 (DIFFIO_RX_L11N/TMS/D3)
V+: C7.1, C10.1, C18.1, C20.1, R9.2, U4.5 (V+), U8.4 (V+), U12.1 (VOUT1), U15.8 (V+)
V-: C8.1, C11.1, C17.1, C19.2, C21.1, D4.1 (A), R11.1, U4.2 (V-), U8.7 (V-), U8.PAD (V-), U15.5 (V-), U15.PAD (V-)
VCOAX: C15.1, C16.1, C23.1, C54.1, C69.1, C75.1, C76.1, J1.2, J2.2, L1.2, L2.2, L12.2, TP12.TP, U3.24 (VDD), U9.3 (EN), U9.4 (IN), U10.3 (EN), U10.4 (IN), U12.3 (VIN), U16.3 (EN), U16.4 (IN), U17.3 (EN), U17.4 (IN), U18.3 (EN), U18.4 (IN), U$1.36, U$1.M3
VDAC: U4.1 (+IN), U7.N3 (AUXIN1), U13.6 (VOUT)
VI: R4.2, U15.7 (OUT)
VSYNC: U11.J4 (DIFFIO_TX_RX_B9N/J4), U19.2 (VSYNC)

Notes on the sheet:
NB: DACx311 recommends 1uF || 0.1uF bypass to reject noise since this is also VREF.
NB: ISTIM = (VDAC - 1.65)/1100. e.g. VDAC = 1.65 -> ISTIM = 0 VDAC = 3.3 -> ISTIM = 1.5 mA VDAC = 0.0 -> ISTIM = -1.5mA
NB: Inductors pass 250mA DC max before they are used to generate a flyback voltage. Because we are dealing with a very low current application, we can probably get away with inductors that saturate below 250 mA so long as they are capable of handling the current. The MLZ2012M100WT000 saturates at 2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
NB: VCoax must NOT exceed 5.5V
NB: We can probably remove the ferrite chip and little bypass caps here. They were from miniscope and may not be applicable since we follow up with LDOs with wideband PSSR and switcher that does not care.
Programming interface
INPUT
ESTIM
OPTOSTIM
SERIALIZER
FPGA
ADC
TRACKING
POWER
TODO: ENV inputs

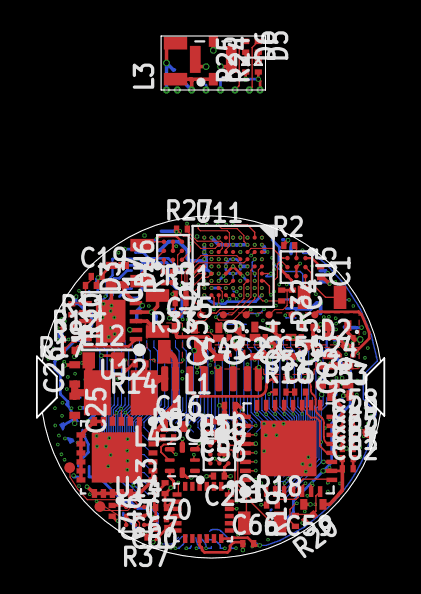
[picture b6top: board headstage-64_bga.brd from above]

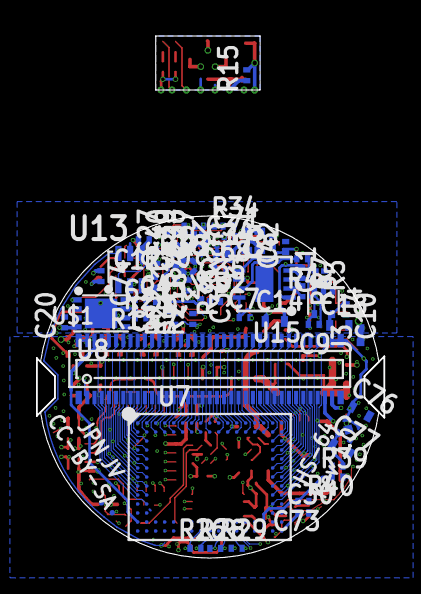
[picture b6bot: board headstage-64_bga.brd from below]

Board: 6 copper layers, 19.3 x 19.0 mm, 168 parts (67 on the bottom side), 183 nets.
